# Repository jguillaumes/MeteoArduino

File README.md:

# MeteoArduino - Small Arduino-Based meteorological station

This project consists on building a basic meteorological monitoring and registering station using an 
Arduino and a few sensors.

It measures the basic weather parameters:
- Temperature
- Atmospheric pressure
- Humidity
- Light level

The data is logged into a microSD card and sent to a nearby receiver using a bluetooth link. The "station" has no user interface, apart from a RESET and a TEST button.

## Materials

### Sensors used

- Temperature sensor, based on a DS18B20 chip.
- Humidity sensor, based on a DHT22 chip. This chip also measures temperature, but that measurement will not be used
- Atmospheric pressure sensor, based on a BMP180 chip
- Light sensor, based on a photoresistor read analogically

### Communications

The device will use an HC-06 based Serial-to-Bluetooth transceiver to send the data it gets to a nearby computer which will do the graphing and reporting.

### Storage

Initial plans called to use a local microSD to store the data in case it could not be transmitted. This is being re-evaluated. The first version will **not** store any data locally.

### Microcontroller

The device will use a nano-Arduino clone as microcontroller. The possibility of using a *raw* MCU will be considered.

## General design

Due to the author soldering (dis)abilities, the different sensors will be bought in ready-to-use format. There are plenty of sources available for that, and they are very cheap.

## General information

The initial design called for a BMP-280 based barometric sensor. Unfortunately that piece of hardware does not tolerate the 5V level of the Arduino board. A bi-directional level converted capable of supporting I2C must be used, and I had no one available. So I switched to the less precise (but good enough) BMP-180, in a breakout form which includes resistors to make it able to stand a 5V signal level. The specific piece is this: https://www.amazon.es/gp/product/B00M1PMSF2/ref=oh_aui_detailpage_o00_s00?ie=UTF8&psc=1

The second version of this project will use a stand-alone ATMega328P running at 8MHz in an all 3.3V circuit so the use of the BMP-280 will be reconsidered.

The BMP-180 branch of this project contains the software adapted for the BMP-180. The master branch uses the BMP-280.

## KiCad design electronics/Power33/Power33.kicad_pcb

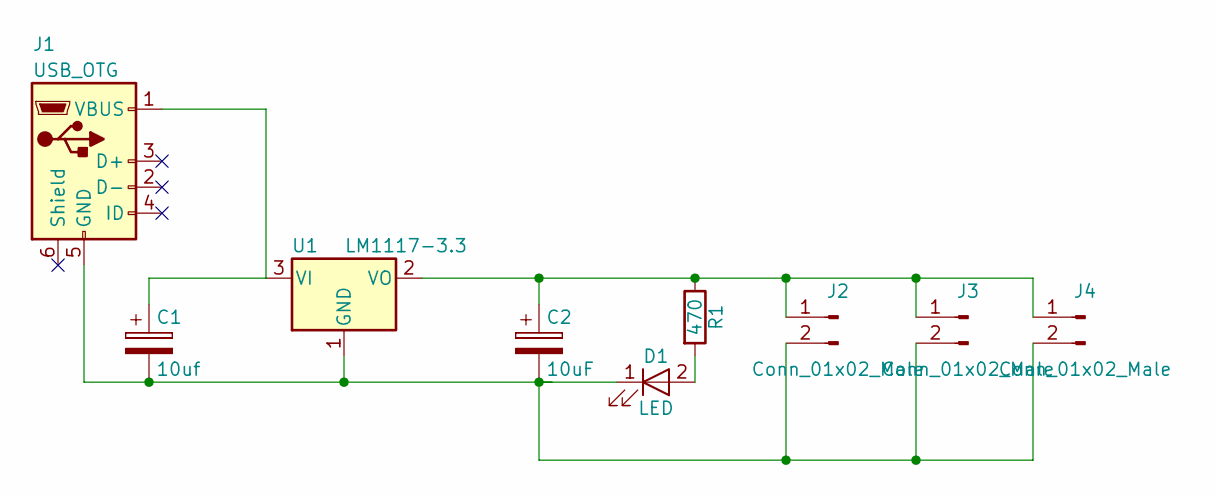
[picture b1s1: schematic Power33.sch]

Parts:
C1: 10uf; CP_Radial_D5.0mm_P2.50mm
C2: 10uF; CP_Radial_D5.0mm_P2.50mm
D1: LED; LED-3MM
J1: USB_OTG; USB_Micro-B_Molex-105017-0001
J2, J3, J4: Conn_01x02_Male; Pin_Header_Straight_1x02_Pitch2.54mm
R1: 470; R_Axial_DIN0414_L11.9mm_D4.5mm_P5.08mm_Vertical
U1: LM1117-3.3; TO-220_Horizontal

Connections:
unnamed: C1.1, J1.1 (VBUS), U1.3 (VI)
unnamed: C1.2, C2.2, D1.1 (K), J1.5 (GND), J2.2, J3.2, J4.2, U1.1 (GND)
unnamed: C2.1, J2.1, J3.1, J4.1, R1.1, U1.2 (VO)
unnamed: D1.2 (A), R1.2

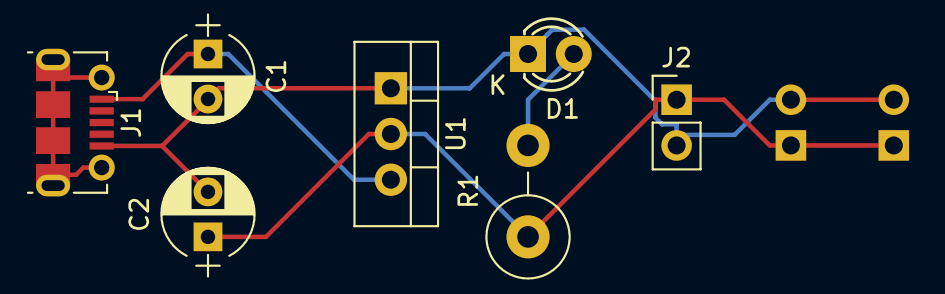
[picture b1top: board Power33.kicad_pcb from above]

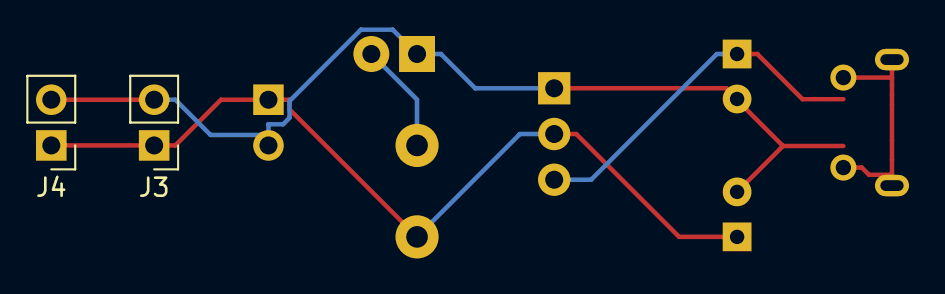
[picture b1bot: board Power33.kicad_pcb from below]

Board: 2 copper layers, 9 parts (2 on the bottom side), 4 nets.

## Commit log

2018-01-18 - Adjust build settings
2018-01-19 - Added barometer reading using Adafruit's BMP280 library
2018-01-28 - Added preliminary support for BT comms
2018-02-01 Add ./Release to .gitignore
2018-02-01 - Removed Release/ from repository - Added light sensor - Changed thermometer PIN to free PIN10 for SPI - Added references to BT comms library and SD logger
2018-02-02 - First (almost) working version. No SD logging by now - Added basic python code to log remotely and to send to elasticsearch
2018-02-02 - Add (preliminary and insufficient) exception handling to weatherClient
2018-02-04 - Added tsa field to weather doc (unique, non opaque identifier) - Added logic to switch to a new index every day - Refactored part of the logic to weatherLib.py
2018-02-05 - Corrected incorrect calls to logMessage() - Added logic for phased retried intervals on BT connection
2018-02-05 Update 'README.md'
2018-02-05 Add .sqlite files to .gitignore
2018-02-05 - Fix several bugs related to logging and exception handlint - The data collected filename is now suffixed with the GMT date and opened for append.
2018-02-06 - Added logic to find the last assigned tsa instead of restarting by zero
2018-02-08 - python: use computed index name all the times instead of default one - Arduino code: conditionally print on Serial() - Add support for standalone microcontroller
2018-02-08 - Improved exception control to keep the process alive in case of ES failure - Refactored functions defined in weatherClient into weatherLib
2018-02-08 - Fix small bug
2018-02-12 - Replace BMP280 by BMP180 pressure sensor (on new branch)
2018-02-12 - Fix misuse of time.sleep() - Add bash script to automatically rerun if aborts
2018-02-12 - README.MD: Clarify the barometric sensor use
2018-02-18 - Old library cleanup - In progress implementation of data recorded based on 23LCV1024 - Add python program to fix bad ES data
2018-02-19 - Replace Adafruit DHTxx library for DHTLib. The Adafruit one does not work well with an MCU clocking at 8MHz - Added functions to read the DHT22 and BMP180 thermometers - Use od BMP180 and DHT22 the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
2018-02-20 - Added support for RTC-less operation. - Changed BT module to HC-05 connected via the UART instead of SoftwareSerial. - Added recovery of sensor failures. The MCU will try to reestablish connection 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
2018-05-01 - Add updateRecords.py
2018-05-05 - Added .dat files to ignore list - Bulk load of records, work in progress
2018-05-07 - Bulk insert of measurements - work in progress:
2018-05-08 - Completed uploadRecords script for uploading bulk measurements
2018-08-28 - Added software clock setting from RTC if available - Fixed fallback for RTC failure - Switched ADC reference to AREF pin
2018-08-29 - Changes for V02.00.00 firmware, new BT address, fix tsa bug
2018-08-29 - Add script to set the gizmo RTC to the current unix time - Stupid tsa fix (again) - Ignore garbage characters instead of abortting on reception
2018-09-09 - Minor corrections
2018-09-11 - Refactoring of weatherClient functions (work in progress)
2018-09-11 - Switch to python logging module - Change index name field in Weather doc (because of name collision) - Correct mishandling of CTRL-C
2018-09-11 - Add comments in some library functions - Add syslog logger - Handle different error messages from the gizmo - Handle gizmo reply to BYE and TIME commands
2018-09-12 - Add README.md to python directory
2018-09-12 - Removed hardcoded addresses and UUIDs and moved them to config file - Removed remaining 'print' statements; now all logging is done using logMessage - Added config file template.
2018-09-12 - Modified version strings
2018-09-12 - Refactored weatherLib - Added subdirectories for database stuff and tools - Moved one-time scripts to tools subdirectory
2018-09-13 - Added support for the queue mechanism (based on sqlite3) - Refactored BlueTooth support (moved into a class)
2018-09-13 - Refactored the DocType subclass (WeatherData) into its own module - Added support for postgresql parameters in the config file - Added class to save data in relational database (postgres) and first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
2018-09-14 - Added TSA assignation from the queue module (and corresponding control table) - Added separate thread to store observations in postgres
2018-09-15 - Changed template name to include the version - Added (again) Elasticsearch support, in a separate thread - Renamed _EL_ stuff to _ES_ (for elasticsearch) - Changed transactionality of sqlite3 acces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
2018-09-16 - Added Janitor and Watchdog threads - INI file reorganization - Added support to be run from any directory - Data files relocated to a ini-specified directory
2018-09-16 - Added database load tool (work in progress) - Minimal tweaks in logging
2018-09-16 - Loader utility uploads to weather_wok table to facilitate cleansing of dupes.
2018-09-16 - Add timezone to time column in pgsql database'
2018-09-16 - Stop threads in case of unexpected exception on main trhread
2018-09-17 - Insert -999.0 values as nulls.
2018-09-17 - Add .search_reset to thermometer preparation. - Check thermometer is present every time.
2018-09-18 - Added Elastic doc Id to the postgres table - Added python tools to update the docId from elasticsearch - Added preliminary support to recover the dupe documents now in weather_dupes - Added Elastic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
2018-09-18 - Check return code from sort utility - Small improvements
2018-09-18 - Added tool to repair documents without TSA
2018-09-19 - Fixed misuse of python reserved name patterns (__*__)
2018-09-19 - Added tool to recover and insert the dupe TSA documents - Added document id generation to the WeatherDB class - Corrected error en tool to recover non-TSAed documents
2018-09-19 - Fixed naming problems - Fixed insertion into db
2018-09-19 - Set esDocId column to not null
2018-09-24 - Refactored watchdog class - BT-reading loop placed in its own thread, which is watched - The time-controlled threads (the janitor and the watchdog) use a Timer object to do their stuff, and check f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
2018-09-25 - Firmware: refactored clock handling into a polymorphic hyerarchy for hardware RTC and software timekeeping - Firmware: this fixes the RTC adjust time bug
2018-09-26 - Added analytics folder
2018-09-26 - The client application has been moved to its own repository.
2018-10-04 - Firmware 03.00.00: Timer/interrupt driven, with watchdog enabled for automatic recovery attempt.
2018-10-05 - Source tree cleanup: sensors and clock source files moved to specific subdirectories
2018-10-06 - Move message text to PROGMEM (in MeteoMessages.h) - Refactor date/time parsing - Add NAME command - Use EEPROM for permanent configuration - Add hardware version and gizmo name to the client message
2018-10-06 - Ooops! The NAME command did not write the EEPROM. Fixed. - Added VERS command to change the hardware version in EEPROM.
2019-01-21 Fw 03.01.00: Add checksum to the DATA message. Closes #9 and TG-13
